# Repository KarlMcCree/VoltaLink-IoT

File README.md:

#  VoltaLink: High-Power AC IoT Timer GenAI Board

**VoltaLink** is a professional, safety-oriented IoT development board that enables **voice** and **manual control** of high-power appliances (up to **30A at 220V/110V**) using AC mains.  
Built on the **ESP32**, VoltaLink connects seamlessly with **Google Home, Alexa, and Siri** for smart home automation, while also offering **local web-based control**.

---

##  Key Features

-  **High-Power Control** – Switches AC loads up to **30A** with an industrial-grade relay safely.  
-  **Voice Assistant Integration** – Works with **Google Assistant, Alexa, Siri** via IoT cloud services.  
-  **Manual & Local Control** – Tactile button + local web interface, independent of the cloud.  
-  **Built-in Safety**:  
  - Galvanic Isolation with Hi-Link AC/DC module.  
  - Fused AC input with protection terminal.  
  - Flyback diode & TVS protection.  

-  **Web Interface** – Simple timer scheduler & manual override.  
-  **Expansion Ready** – I²C, UART, and GPIO headers for sensors or displays.  

---

##  Technical Specifications

| Parameter              | Specification                     |
|-------------------------|-----------------------------------|
| **Microcontroller**     | ESP32-WROOM-32D                  |
| **WiFi Connectivity**   | 802.11 b/g/n (2.4 GHz)           |
| **Input Voltage**       | 110V / 220V AC (50/60 Hz)        |
| **Output Rating**       | 30A Max, 250V AC                 |
| **Low-Voltage Logic**   | 3.3V & 5V DC                     |
| **Control Interfaces**  | Voice, Web Server, Physical Btn  |
| **Safety Features**     | Fuse, Optoisolation, Flyback, Creepage Clearance |

---

##  Hardware Overview

The PCB is carefully designed with **high-voltage (right)** and **low-voltage (left)** separation for safety.  

- **AC Terminal Blocks** – Safe connection of mains wiring.  
- **Fuse Holder** – Over-current protection.  
- **Hi-Link HLK-PM05** – Isolated 220V → 5V power supply.  
- **ESP32-WROOM-32D** – Core WiFi + control logic.  
- **Industrial Relay (RAYEX-L90)** – 30A switching.  
- **Optoisolator (PC817)** – Isolation between control & relay.  
- **Manual Button** – Local timer & override control.  
- **LED + Buzzer** – User feedback indicators.  
- **I²C Header** – Expansion for OLED display or sensors.  

---

##  Software & Firmware

The firmware is built on the **Arduino Core for ESP32** and provides:

-  **Web Configuration Portal** – Configure timers via browser.  
-  **NTP Sync** – Automatic time synchronization.  
-  **EEPROM Storage** – Saves timer schedules across reboots.  
- 🔗 **RESTful API** – Integrates with external smart home systems.  

---

##  Safety Warning  

 **HIGH VOLTAGE NOTICE** 

This project works with **LETHAL MAINS VOLTAGE (110V/220V AC)**.  
**Do NOT attempt** unless you are qualified and aware of the safety precautions.  

**Always follow these rules:**  
-  Work **de-energized** – Never solder/test while powered.  
-  Use a **proper insulated enclosure**.  
-  Ensure **proper grounding**.  
-  Test with **GFCI outlets** and current-limited supply.  

---

##  Future Enhancements

-  CT sensor integration for **energy monitoring**.  
-  **BLE provisioning** for easy setup.  
-  **OTA firmware updates**.  
-  PCB-mount **temperature sensor** for thermal protection.  
-  **4-layer board** design for improved EMC performance.  

---

##  Contributing

Pull requests, issues, and feature suggestions are welcome!  
Donations to support the development are also appreciated.  

---

##  License  

This project is released for **educational purposes only**.  
 Use at your own risk when working with mains power.

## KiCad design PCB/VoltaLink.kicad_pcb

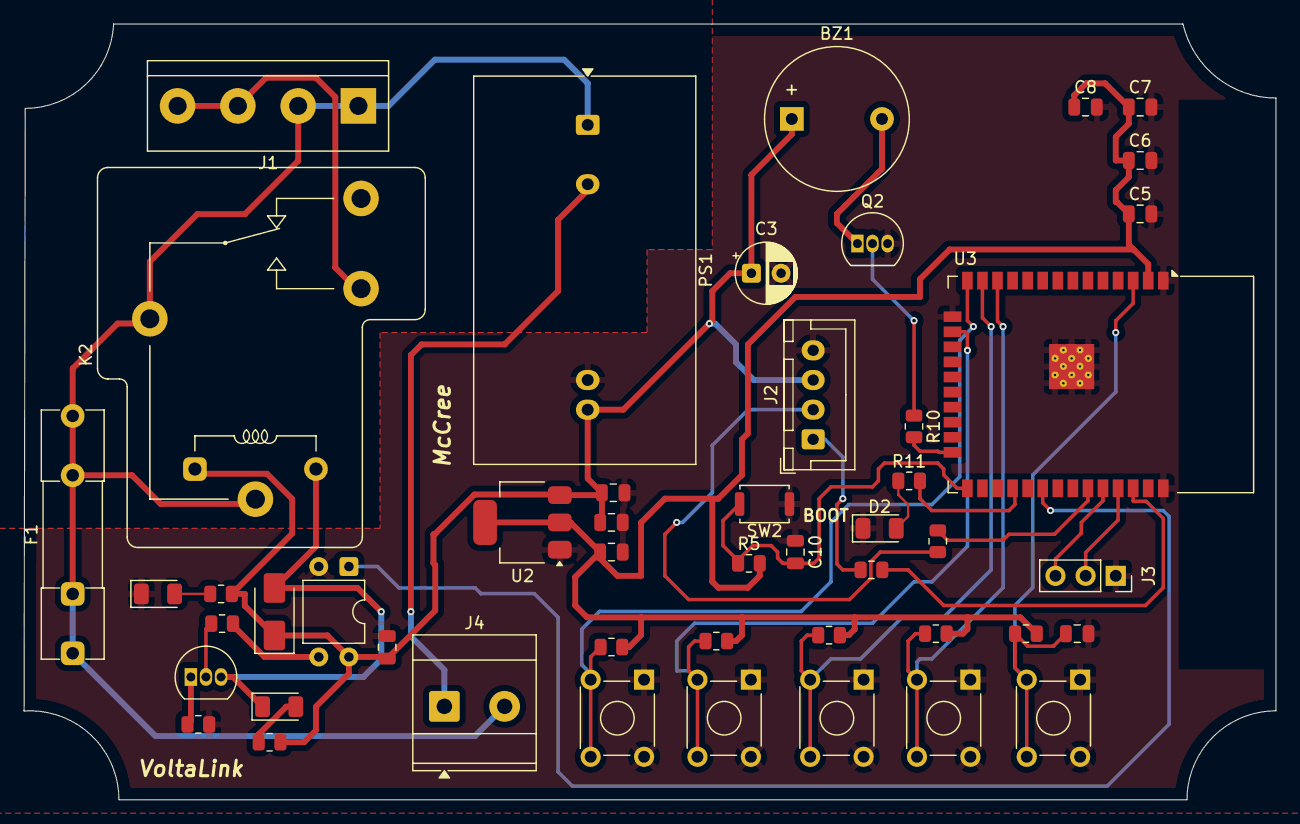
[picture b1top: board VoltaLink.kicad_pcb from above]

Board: 2 copper layers, 105.5 x 65.4 mm, 48 parts (0 on the bottom side), 30 nets.

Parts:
BZ1: Buzzer; Buzzer_12x9.5RM7.6
C1, C6, C7, C8, C9, C10, C11: 0.1uF; C_0805_2012Metric
C2, C4, C5: 10uF; C_0805_2012Metric
C3: 100uF; CP_Radial_D5.0mm_P2.50mm
D1, D2, D3: LED; LED_1206_3216Metric
D4: SS24; D_SMA
F1: 2A; Fuseholder_Clip-5x20mm_Littelfuse_111_Inline_P20.00x5.00mm_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
J1: Screw_Terminal_01x04; TerminalBlock_bornier-4_P5.08mm
J2: Conn_01x04_Pin; JST_XH_B4B-XH-A_1x04_P2.50mm_Vertical
J3: Conn_01x03_Pin; PinSocket_1x03_P2.54mm_Vertical
J4: Screw_Terminal_01x02; TerminalBlock_Phoenix_MKDS-3-2-5.08_1x02_P5.08mm_Horizontal
K2: RAYEX-L90; Relay_SPDT_RAYEX-L90
PS1: HLK-2M05; Converter_ACDC_Hi-Link_HLK-2Mxx
Q1, Q2: PN2222A; TO-92_Inline
R1: 220Ω; R_0805_2012Metric
R2: 2.2kΩ; R_0805_2012Metric
R3: 1k; R_0805_2012Metric
R4, R5, R6, R7, R8, R9, R16: 10kΩ; R_0805_2012Metric
R10: 330Ω; R_0805_2012Metric
R11: 1kΩ; R_0805_2012Metric
R12, R13: 4.7kΩ; R_0805_2012Metric
SW1, SW3, SW4, SW5, SW6: SW_Push; SW_TH_Tactile_Omron_B3F-10xx
SW2: SW_Push; SW_Push_SPST_NO_Alps_SKRK
U1: PC817; DIP-4_W7.62mm
U2: AMS1117-3.3; SOT-223-3_TabPin2
U3: ESP32-WROOM-32D

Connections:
+5V_RAW: BZ1.1 (+), C1.1, C2.1, C3.1, C11.1, D4.1 (K), J2.3, K2.A1, PS1.4 (+Vout), R1.1, R3.1, U1.4, U2.3 (VI)
AC_L_FUSED: F1.1, F1.2, J1.1, J1.2, J4.2, K2.11A, K2.11B, PS1.1 (AC/L)
AC_L_OUT: J1.3, J1.4, K2.14
AC_N_IN: J4.1, PS1.2 (AC/N)
BTN/IO12: R6.1, SW3.2, U3.14 (IO12)
BTN/IO13: R7.1, SW4.2, U3.16 (IO13)
BTN/IO14: R8.1, SW5.2, U3.13 (IO14)
BTN/IO27: R9.1, SW6.2, U3.12 (IO27)
BUZZER_CTRL: R10.2, U3.24 (IO2)
EN/RESET: C9.2, R4.1, SW1.2, U3.3 (EN)
GND: C1.2, C2.2, C3.2, C4.2, C5.2, C6.2, C7.2, C8.2, C9.1, C10.1, C11.2, D1.1 (K), D2.1 (K), J2.4, J3.1, PS1.3 (-Vout), Q2.3 (C), R16.1, SW1.1, SW2.1, SW3.1, SW4.1, SW5.1, SW6.1, U1.2, U2.1 (GND), U3.1 (GND), U3.15 (GND), U3.38 (GND), U3.39 (GND)
IO0/BOOT: C10.2, R5.1, SW2.2, U3.25 (IO0)
LED_STATUS: R11.2, U3.28 (IO17)
MCL_3.3V: C4.1, C5.1, C6.1, C7.1, C8.1, R4.2, R5.2, R6.2, R7.2, R8.2, R9.2, U2.2 (VO), U3.2 (VDD)
unnamed: BZ1.2 (-), Q2.1 (E)
unnamed: D1.2 (A), R1.2
unnamed: D2.2 (A), R11.1
unnamed: D3.2 (A), R3.2
unnamed: D3.1 (K), D4.2 (A), K2.A2, Q1.3 (C)
unnamed: J2.1, R13.2
unnamed: J2.2, R12.2
unnamed: Q1.2 (B), R2.2
unnamed: Q1.1 (E), R16.2
unnamed: Q2.2 (B), R10.1
unnamed: R2.1, U1.3
RELAY_CTRL: U1.1, U3.30 (IO18)
RXD: J3.3, U3.34 (RXD0/IO3)
SCL/IO22: R13.1, U3.36 (IO22)
SDA/IO21: R12.1, U3.33 (IO21)
TXD: J3.2, U3.35 (TXD0/IO1)
